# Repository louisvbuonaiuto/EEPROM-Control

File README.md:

# EEPROM-Control

The goal of this project is to further test EEPROMs of different packages and memory sizes.

This respository is a continuation of [Fraser Dougalls SPR-24-RADHARD-Research](https://github.com/FraserD404/Spr24-RadHard-Research.git) for EEPROM Control. 

### TODO: 
- Save specific EEPROM to CSV
- research previous EEPROM Pi setups

### connecting to neutronPi
Currently the neutronPi (Raspberry Pi 4) has a headless configuration with Raspberry Pi OS Lite (64-bit) 
Louis Buonaiuto Purdue Pal3.0 login
note sometimes ssh doesn't work since some buildings block ssh. Some PAL3.0 work some don't
ssh to pi "$ ssh louis@neutronPi.local" password: 5682

## Resources

### wiringPi

### PI 5

[GPIO Pinout](https://www.raspberrypi.com/documentation/computers/raspberry-pi.html#gpio)
>EEPROM Data: (GPIO0); EEPROM Clock (GPIO1)

### I<sup>2</sup>C
- [Understanding I2C](https://www.youtube.com/watch?v=CAvawEcxoPU)
- https://learn.sparkfun.com/tutorials/i2c
- https://learn.sparkfun.com/tutorials/raspberry-pi-spi-and-i2c-tutorial

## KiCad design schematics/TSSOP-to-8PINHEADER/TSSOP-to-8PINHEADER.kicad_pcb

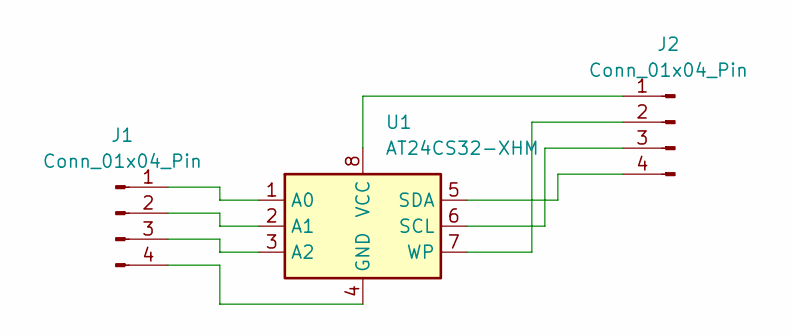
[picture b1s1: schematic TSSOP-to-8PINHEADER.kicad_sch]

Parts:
J1, J2: Conn_01x04_Pin; PinHeader_1x04_P2.54mm_Vertical
U1: AT24CS32-XHM; TSSOP-8_4.4x3mm_P0.65mm

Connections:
unnamed: J1.1, U1.1 (A0)
unnamed: J1.2, U1.2 (A1)
unnamed: J1.3, U1.3 (A2)
unnamed: J1.4, U1.4 (GND)
unnamed: J2.1, U1.8 (VCC)
unnamed: J2.2, U1.7 (WP)
unnamed: J2.3, U1.6 (SCL)
unnamed: J2.4, U1.5 (SDA)

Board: 2 copper layers, 3 parts (2 on the bottom side), 8 nets, no tracks yet.

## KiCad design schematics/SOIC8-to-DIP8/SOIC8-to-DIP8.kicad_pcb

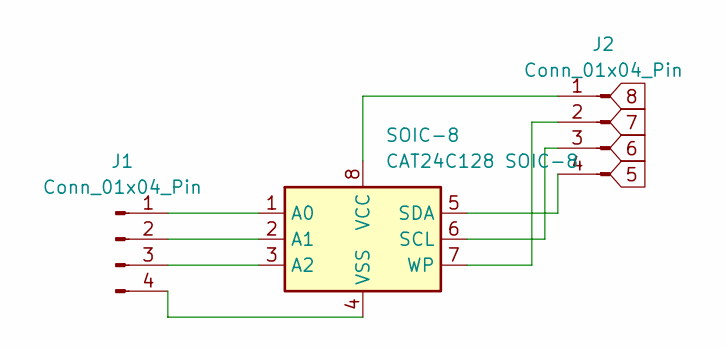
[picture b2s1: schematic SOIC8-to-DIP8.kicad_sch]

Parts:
J1, J2: Conn_01x04_Pin; PinHeader_1x04_P2.54mm_Vertical
SOIC-8: CAT24C128 SOIC-8; SOIC-8-1EP_3.9x4.9mm_P1.27mm_EP2.41x3.81mm_1

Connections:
unnamed: J1.1, SOIC-8.1 (A0)
unnamed: J1.2, SOIC-8.2 (A1)
unnamed: J1.3, SOIC-8.3 (A2)
unnamed: J1.4, SOIC-8.4 (VSS)
unnamed: J2.1, SOIC-8.8 (VCC)
unnamed: J2.2, SOIC-8.7 (WP)
unnamed: J2.3, SOIC-8.6 (SCL)
unnamed: J2.4, SOIC-8.5 (SDA)

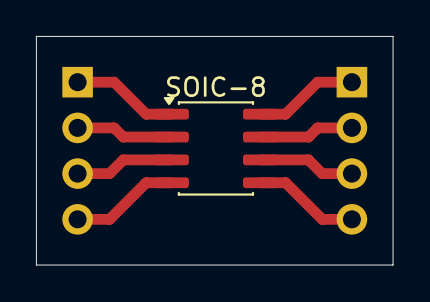
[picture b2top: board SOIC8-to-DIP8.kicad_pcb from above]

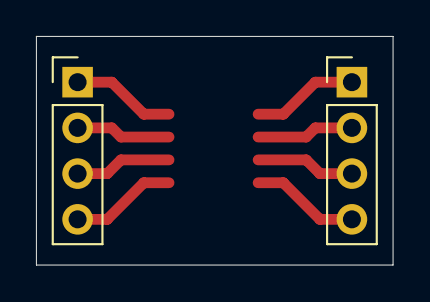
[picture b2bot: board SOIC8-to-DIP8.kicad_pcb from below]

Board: 2 copper layers, 19.8 x 12.7 mm, 3 parts (2 on the bottom side), 8 nets.

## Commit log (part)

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2026-06-16 organized old files, improved csv file saving struture in EEPROM-ctrl-virutal.c
2026-06-22 update EEPROM-ctrl-virtual.c code to test on Pi5
2026-06-29 add schematics and datasheets, EEPROM-Connection-Test.c for testing EEPROM connection
2026-06-29 add wiringPi-testing/
